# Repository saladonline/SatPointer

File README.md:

The ISS Orbital Tracker Workshop will guide attendees through assembling an automated robotic pointer that tracks the location of the International Space Station in real time. The workshop will be divided into two parts. Part 1 covers the science behind orbital mechanics, and gives background on the project itself. Part 2 is a hands-on section where attendees are provided with the materials to build their own orbital pointer, and are guided through assembly and programming of the device.

Prepared by Salvador Vasquez

### Hardware
- ESP8266
- Stepper motor
	- Driver
- Servomotor

### Software
- SGP4
	- Orbital math
	- Coordinate systems
- Azimuth: Stepper
- Elevation: Servo
- Updating TLE
	- From internet: [Link](https://www.celestrak.org/NORAD/elements/gp.php?CATNR=25544&FORMAT=TLE)
	- By hand
	- Tracking different satellites

# Budget

| Item | Description     | Cost   | Link |
|------|-----------------|--------|------|
| 1    | ESP8266         | $2.68  | [Link](https://share.temu.com/dwIEmbCtYWA) |
| 2    | Stepper         | $0.61  | [Link](https://www.aliexpress.us/item/3256804755489791.html) |
| 3    | Servo           | $1.22  | [Link](https://www.aliexpress.us/item/3256804364197715.html) |
| 4    | Stepper Driver  | $0.64  | [Link](https://www.digikey.com/short/zwjfqjd0) |
| 5    | Slip Ring       | $2.57  | [Link](https://www.aliexpress.us/item/3256802527929967.html) |
| 6    | Micro USB cable | $0.86  | [Link](https://share.temu.com/fXmrZp8YbyA) |
| 7    | 5W power brick  | $1.49  | [Link](https://share.temu.com/9dzaBk76MuA) |
| 8    | PCB             | $1.12  | [Link](https://github.com/saladonline/SatPointer) |
| 9    | JST Connector   | $0.05  | [Link](https://www.aliexpress.us/item/3256805938058599.html) |
|      | Total           | $12.00 |

# Resources
[Orbital Mechanics Tutorials](http://celestrak.org/columns/)
[SGP4 Academic paper](https://celestrak.org/publications/AIAA/2008-6770/AIAA-2008-6770.pdf)
[Original source code in C++](https://github.com/gradyh/ISS-Tracking-Pointer/tree/master)
[NORAD Satellite Data](https://celestrak.org/NORAD/elements/)

# Updates
- Found cheaper slip ring
- Added PCB
- ~~Changed RPi Pico W for ESP8266~~
- ~~Added USB cable to materials~~
- ~~Added more info on TLE section~~

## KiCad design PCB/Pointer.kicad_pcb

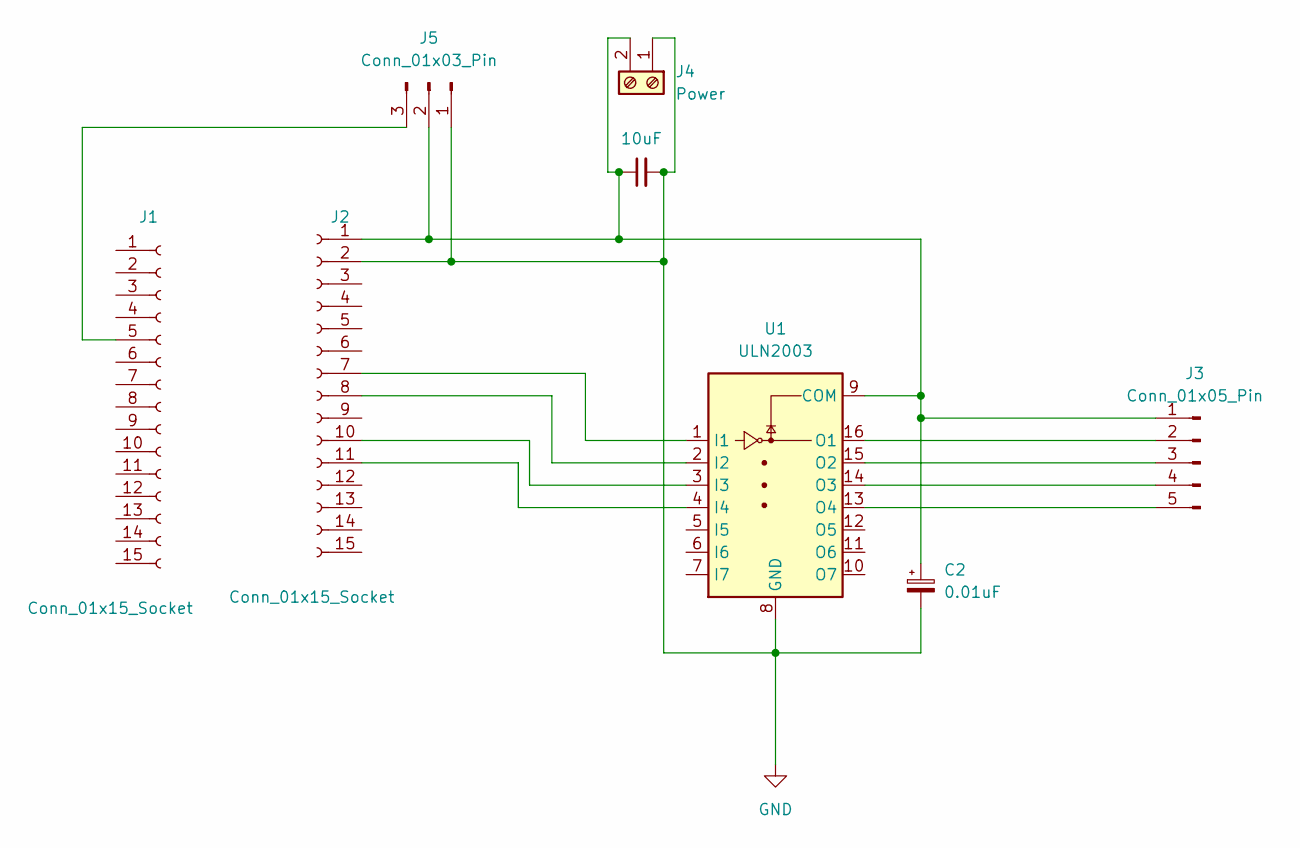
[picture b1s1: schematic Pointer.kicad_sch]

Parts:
C1: 10uF; C_Axial_L3.8mm_D2.6mm_P7.50mm_Horizontal
C2: 0.01uF; CP_Radial_D4.0mm_P1.50mm
J1, J2: Conn_01x15_Socket; PinSocket_1x15_P2.54mm_Vertical
J3: Conn_01x05_Pin; JST_XH_B5B-XH-A_1x05_P2.50mm_Vertical
J4: Power; TerminalBlock_Phoenix_MKDS-1,5-2-5.08_1x02_P5.08mm_Horizont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
J5: Conn_01x03_Pin; PinHeader_1x03_P2.54mm_Vertical
U1: ULN2003; DIP-16_W7.62mm_Socket

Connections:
GND: C1.2, C2.2, J2.2, J4.1, J5.1, U1.8 (GND)
unnamed: J1.5, J5.3
unnamed: C1.1, C2.1, J2.1, J3.1, J4.2, J5.2, U1.9 (COM)
unnamed: J2.7, U1.1 (I1)
unnamed: J2.8, U1.2 (I2)
unnamed: J2.10, U1.3 (I3)
unnamed: J2.11, U1.4 (I4)
unnamed: J3.2, U1.16 (O1)
unnamed: J3.3, U1.15 (O2)
unnamed: J3.4, U1.14 (O3)
unnamed: J3.5, U1.13 (O4)

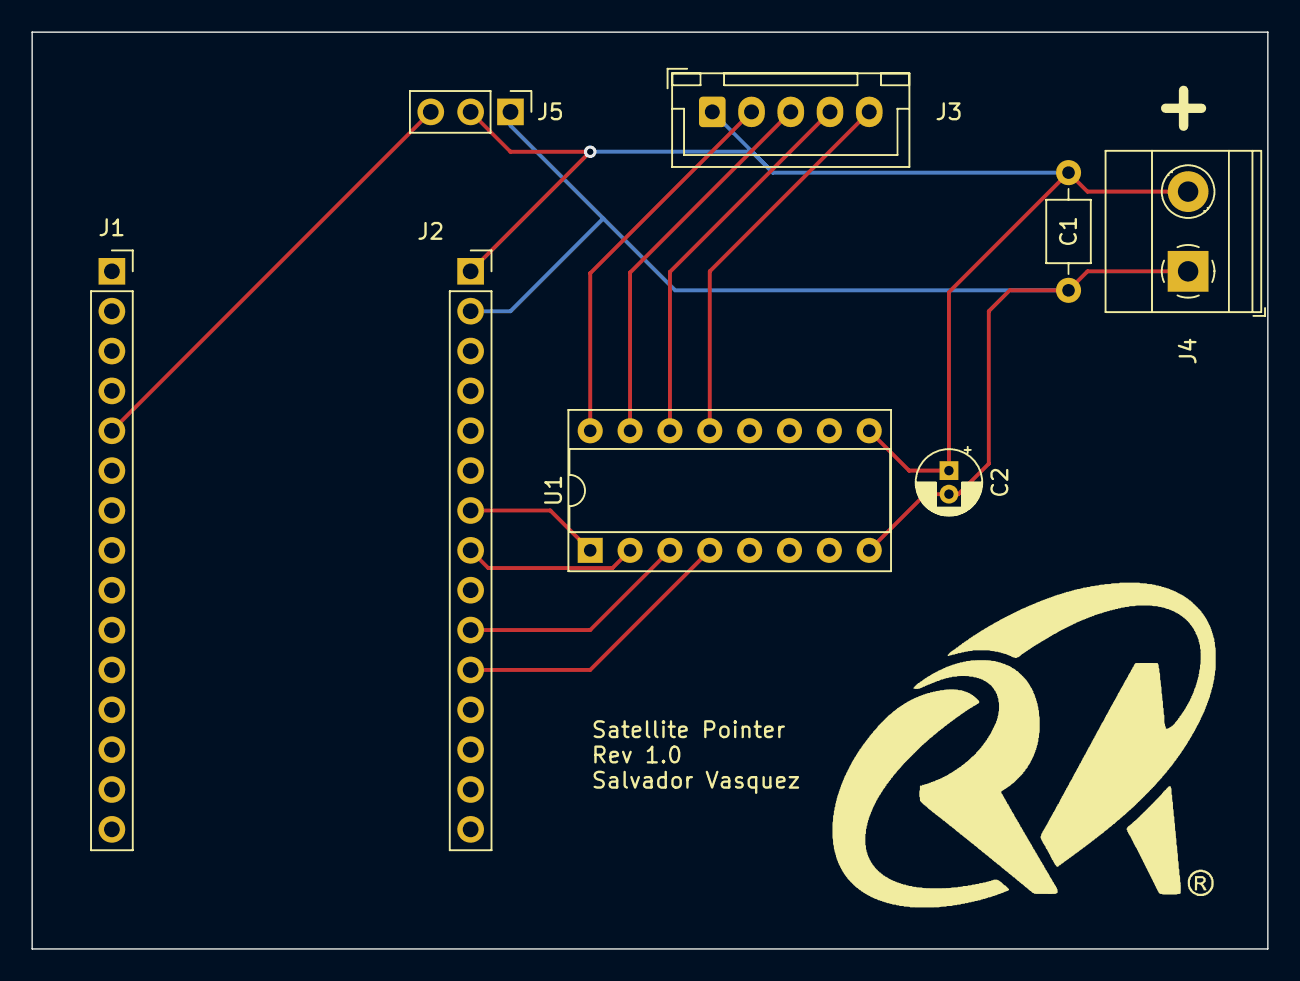
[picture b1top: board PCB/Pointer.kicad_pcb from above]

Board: 2 copper layers, 78.7 x 58.4 mm, 9 parts (0 on the bottom side), 11 nets.

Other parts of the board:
Logo: LOGO

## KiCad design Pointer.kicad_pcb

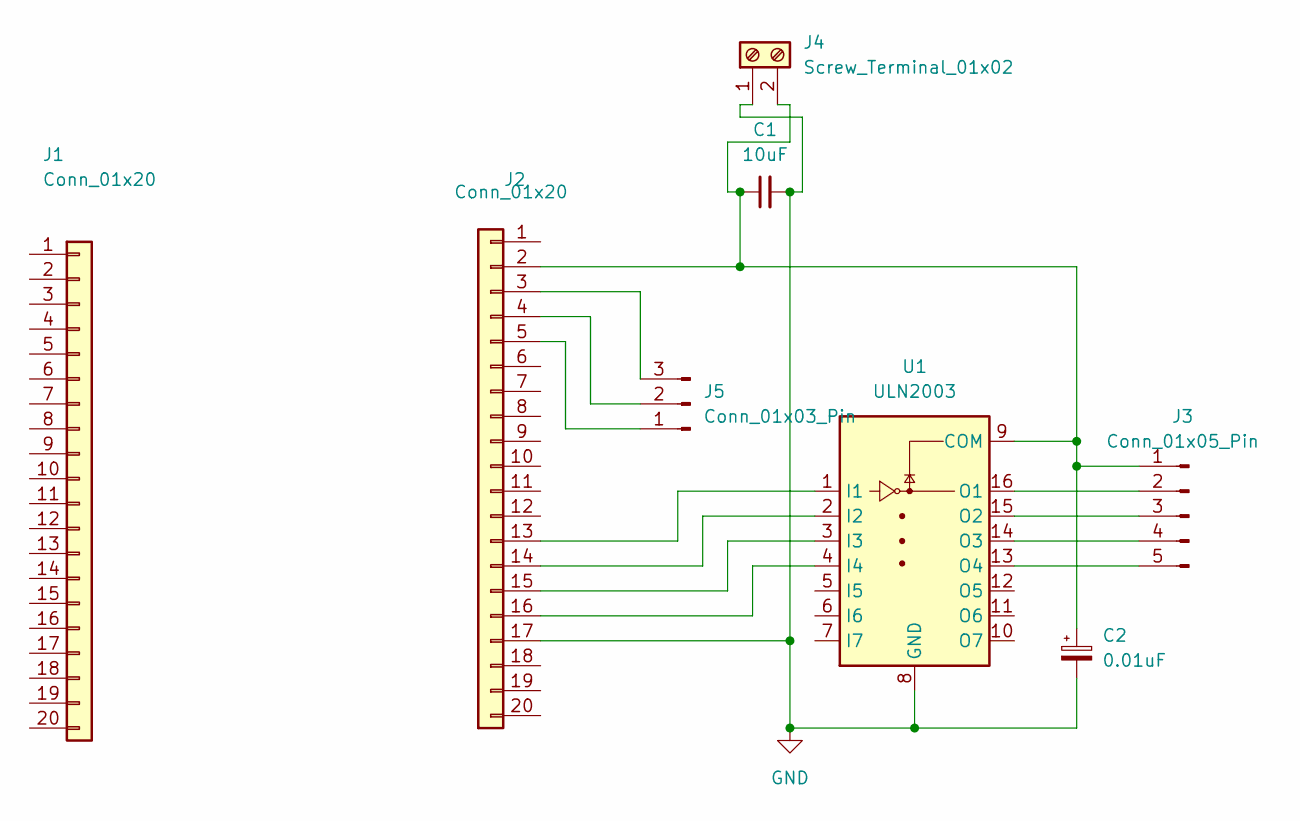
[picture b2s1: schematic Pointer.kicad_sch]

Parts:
C1: 10uF; C_Axial_L3.8mm_D2.6mm_P7.50mm_Horizontal
C2: 0.01uF; CP_Radial_D4.0mm_P1.50mm
J1, J2: Conn_01x20; PinSocket_1x20_P2.54mm_Vertical
J3: Conn_01x05_Pin; JST_XH_B5B-XH-A_1x05_P2.50mm_Vertical
J4: Screw_Terminal_01x02; TerminalBlock_Phoenix_MKDS-1,5-2-5.08_1x02_P5.08mm_Horizont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
J5: Conn_01x03_Pin; PinHeader_1x03_P2.54mm_Vertical
U1: ULN2003; DIP-16_W7.62mm_Socket

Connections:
GND: C1.2, C2.2, J2.17, J4.1, U1.8 (GND)
unnamed: C1.1, C2.1, J2.2, J3.1, J4.2, U1.9 (COM)
unnamed: J2.3, J5.3
unnamed: J2.4, J5.2
unnamed: J2.5, J5.1
unnamed: J2.13, U1.1 (I1)
unnamed: J2.14, U1.2 (I2)
unnamed: J2.15, U1.3 (I3)
unnamed: J2.16, U1.4 (I4)
unnamed: J3.2, U1.16 (O1)
unnamed: J3.3, U1.15 (O2)
unnamed: J3.4, U1.14 (O3)
unnamed: J3.5, U1.13 (O4)

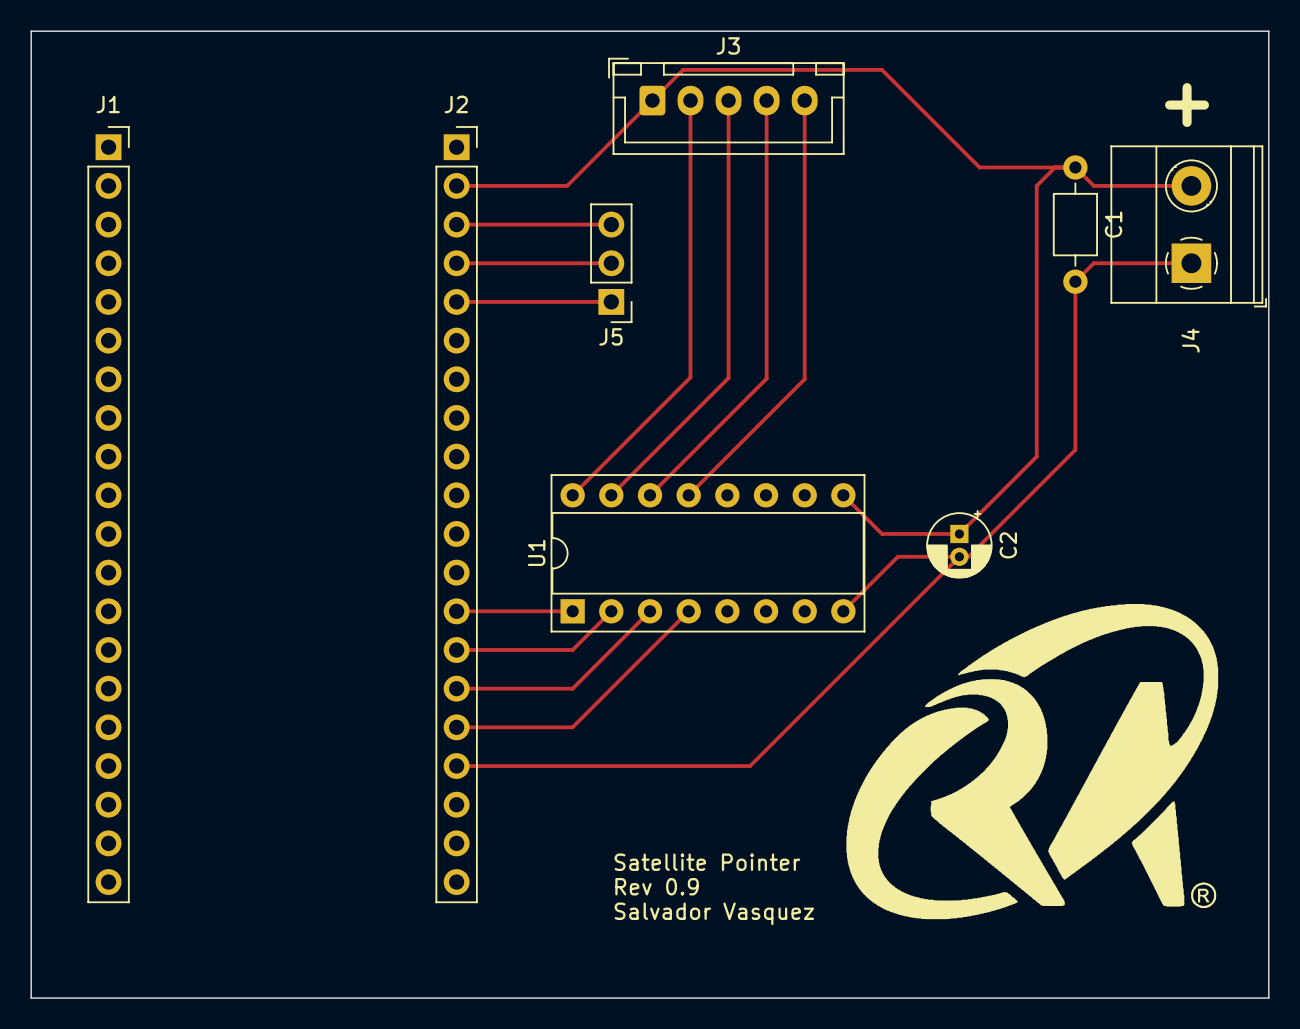
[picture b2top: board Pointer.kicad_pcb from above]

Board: 2 copper layers, 81.3 x 63.5 mm, 9 parts (0 on the bottom side), 13 nets.

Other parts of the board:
Logo: LOGO

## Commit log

2023-12-05 Update README.md
    Initial upload
2023-12-05 Added Initial PCB Schematics
    TODO: Place new headers for ESP8266
2023-12-05 Create blank
2023-12-05 Moved schematic to PCB folder
2023-12-05 Update and rename Pointer.kicad_sch to PCB/Pointer.kicad_sch
    Moved Schematic to PCB folder
2023-12-05 KiCad project fix
    Uploaded all files in KiCad project folder
2023-12-05 PCB Rev 1.0
    Fixed MCU and servo headers
2023-12-06 Update LICENSE
